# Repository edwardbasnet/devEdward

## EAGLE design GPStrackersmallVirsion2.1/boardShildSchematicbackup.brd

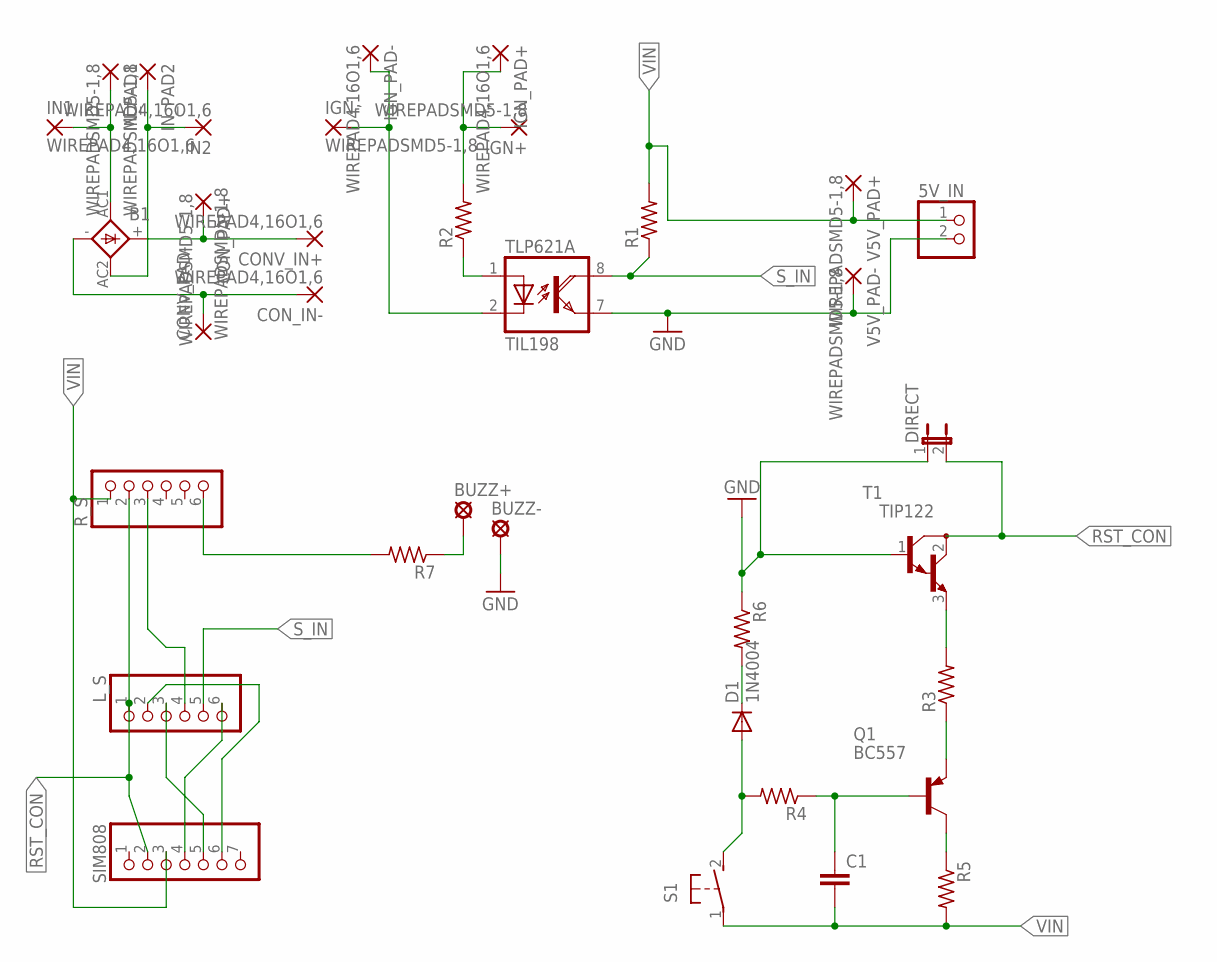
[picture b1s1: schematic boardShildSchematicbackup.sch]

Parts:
5V_IN: PINHD-1X2; 1X02
B1: FB15
BUZZ+: LSP10
BUZZ-: LSP10
C1: C2.5/5; C2.5-5
CONV_IN+: WIREPAD4,16O1,6; 4,16O1,6
CONV_PAD-: WIREPADSMD5-1,8; 5-1,8
CON_IN-: WIREPAD4,16O1,6; 4,16O1,6
CON_PAD+: WIREPADSMD5-1,8; 5-1,8
D1: 1N4004; DO41-10
DIRECT: JP1E; JP1
IGN+: WIREPADSMD5-1,8; 5-1,8
IGN-: WIREPADSMD5-1,8; 5-1,8
IGN_PAD+: WIREPAD4,16O1,6; 4,16O1,6
IGN_PAD-: WIREPAD4,16O1,6; 4,16O1,6
IN1, IN2: WIREPAD4,16O1,6; 4,16O1,6
IN_PAD1, IN_PAD2: WIREPADSMD5-1,8; 5-1,8
L_S: PINHD-1X6; 1X06
Q1: BC557; TO92
R1, R2, R3, R4, R5, R6, R7: R-US_0204/5; 0204/5
R_S: PINHD-1X6; 1X06
S1: 31-XX; B3F-31XX
SIM808: PINHD-1X7; 1X07
T1: TIP122; TO220
TLP621: TIL198; DIL08
V5V_PAD+, V5V_PAD-: WIREPADSMD5-1,8; 5-1,8

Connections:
GND: 5V_IN.2, BUZZ-.MP, DIRECT.1, R6.1, T1.1 (B), TLP621.7 (EMI), V5V_PAD-.1
unnamed: R2.1, TLP621.1 (A)
unnamed: B1.AC1, IN1.1, IN_PAD1.1
unnamed: IGN+.1, IGN_PAD+.1, R2.2
unnamed: L_S.4, R_S.3
unnamed: L_S.2, SIM808.6
unnamed: B1.-, CONV_PAD-.1, CON_IN-.1
unnamed: L_S.3, SIM808.5
unnamed: L_S.6, SIM808.4
unnamed: IGN-.1, IGN_PAD-.1, TLP621.2 (C)
unnamed: BUZZ+.MP, R7.1
unnamed: B1.AC2, IN2.1, IN_PAD2.1
unnamed: D1.A, R4.2, S1.2 (S)
unnamed: C1.1, Q1.2 (B), R4.1
unnamed: B1.+, CONV_IN+.1, CON_PAD+.1
unnamed: Q1.3 (C), R5.1
unnamed: Q1.1 (E), R3.1
unnamed: D1.C, R6.2
unnamed: R7.2, R_S.6
unnamed: R3.2, T1.3 (E)
RST_CON: DIRECT.2, L_S.1, R_S.2, SIM808.2, T1.2 (C)
S_IN: L_S.5, R1.1, TLP621.8 (COL)
VIN: 5V_IN.1, C1.2, R1.2, R5.2, R_S.1, S1.1, SIM808.3, V5V_PAD+.1

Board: 2 copper layers, 35 parts (0 on the bottom side), 23 nets, no tracks yet.

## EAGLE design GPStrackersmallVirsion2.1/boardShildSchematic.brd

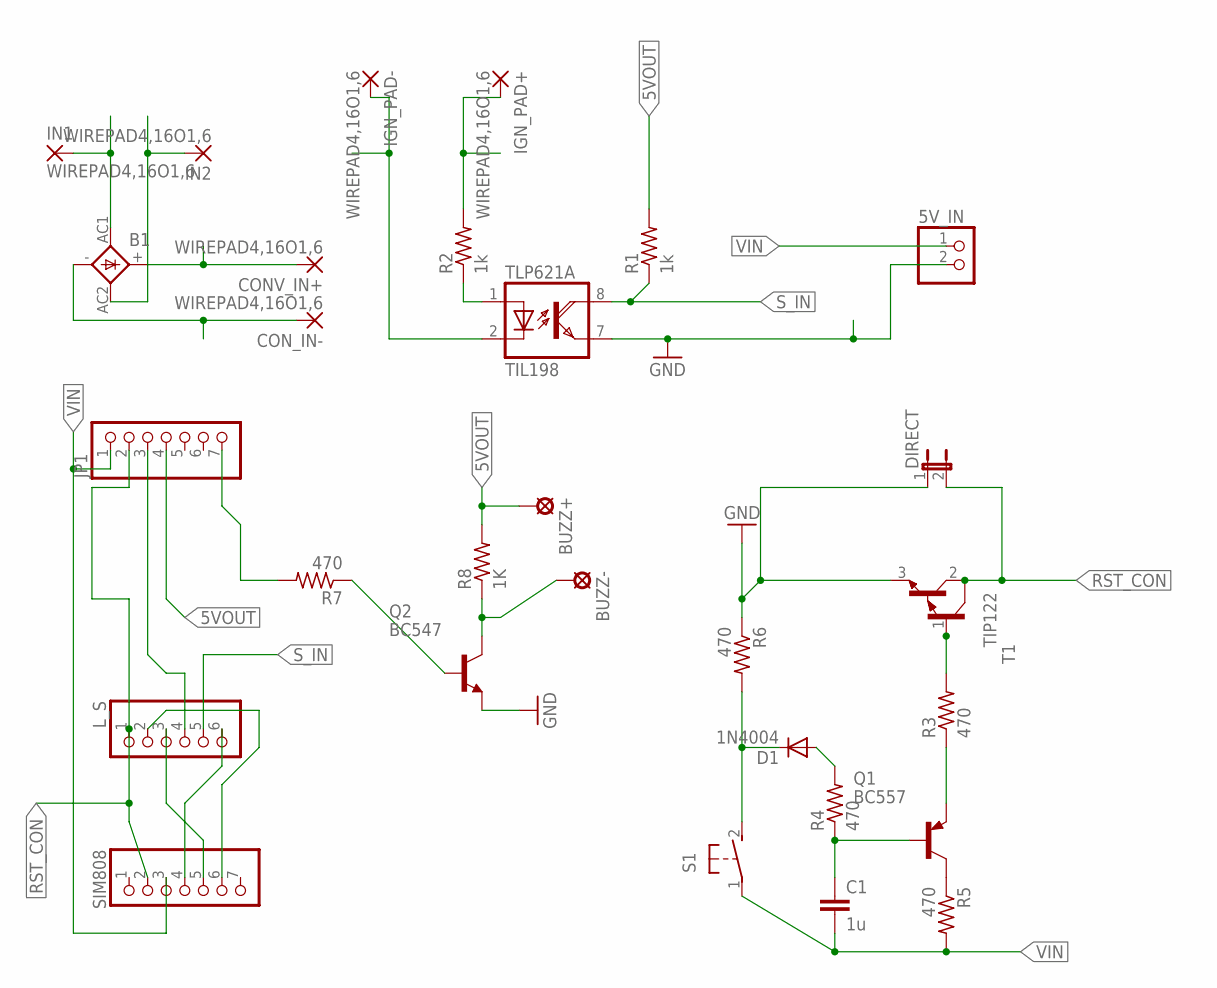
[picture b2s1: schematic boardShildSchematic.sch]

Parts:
5V_IN: PINHD-1X2; 1X02
B1: FB15
BUZZ+: LSP10
BUZZ-: LSP10
C1: 1u; C2.5-5
CONV_IN+: WIREPAD4,16O1,6; 4,16O1,6
CON_IN-: WIREPAD4,16O1,6; 4,16O1,6
D1: 1N4004; DO41-10
DIRECT: JP1E; JP1
IGN_PAD+: WIREPAD4,16O1,6; 4,16O1,6
IGN_PAD-: WIREPAD4,16O1,6; 4,16O1,6
IN1, IN2: WIREPAD4,16O1,6; 4,16O1,6
JP1: PINHD-1X7; 1X07
L_S: PINHD-1X6; 1X06
Q1: BC557; TO92
Q2: BC547; TO92
R1, R2: 1k; 0204/5
R3, R4, R5, R6, R7: 470; 0204/5
R8: 1K; 0204/5
S1: 31-XX; B3F-31XX
SIM808: PINHD-1X7; 1X07
T1: TIP122; TO220
TLP621: TIL198; DIL08

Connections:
5VOUT: BUZZ+.MP, JP1.4, R1.2, R8.2
GND: 5V_IN.2, DIRECT.1, Q2.1 (E), R6.1, T1.3 (E), TLP621.7 (EMI)
unnamed: R2.1, TLP621.1 (A)
unnamed: B1.AC1, IN1.1
unnamed: IGN_PAD+.1, R2.2
unnamed: JP1.3, L_S.4
unnamed: L_S.2, SIM808.6
unnamed: B1.-, CON_IN-.1
unnamed: L_S.3, SIM808.5
unnamed: L_S.6, SIM808.4
unnamed: IGN_PAD-.1, TLP621.2 (C)
unnamed: Q2.2 (B), R7.1
unnamed: B1.AC2, IN2.1
unnamed: D1.A, R4.2
unnamed: C1.1, Q1.2 (B), R4.1
unnamed: B1.+, CONV_IN+.1
unnamed: Q1.3 (C), R5.1
unnamed: Q1.1 (E), R3.1
unnamed: D1.C, R6.2, S1.2 (S)
unnamed: JP1.7, R7.2
unnamed: R3.2, T1.1 (B)
unnamed: BUZZ-.MP, Q2.3 (C), R8.1
RST_CON: DIRECT.2, JP1.2, L_S.1, SIM808.2, T1.2 (C)
S_IN: L_S.5, R1.1, TLP621.8 (COL)
VIN: 5V_IN.1, C1.2, JP1.1, R5.2, S1.1, SIM808.3

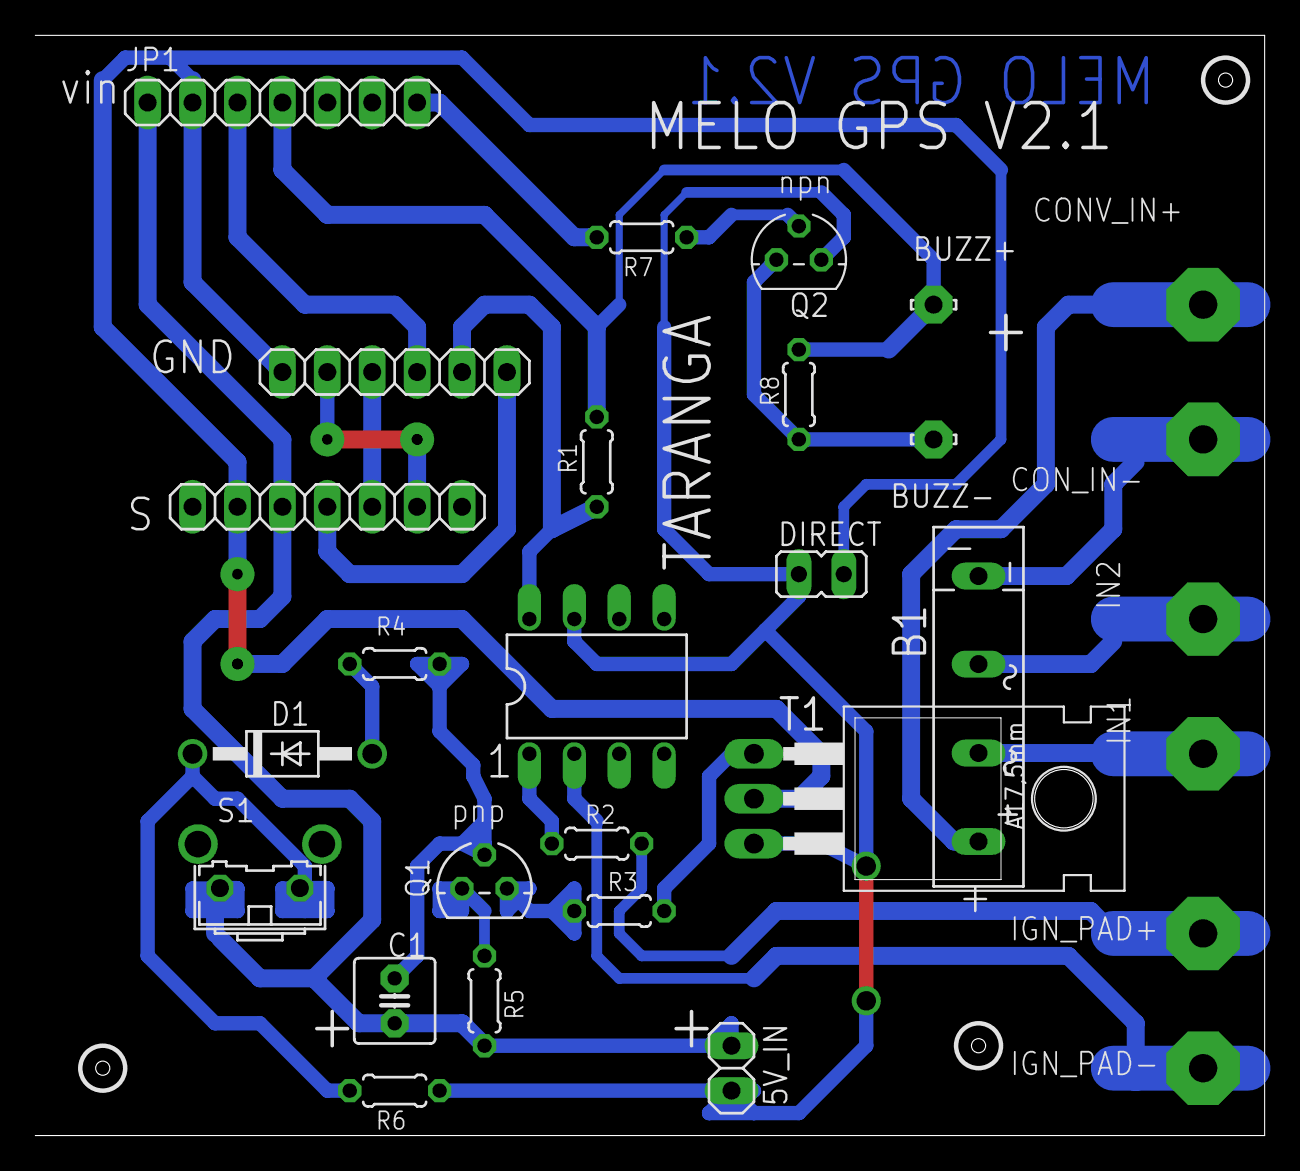
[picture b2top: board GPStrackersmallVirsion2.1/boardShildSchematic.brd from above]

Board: 2 copper layers, 69.5 x 62.2 mm, 29 parts (0 on the bottom side), 25 nets.

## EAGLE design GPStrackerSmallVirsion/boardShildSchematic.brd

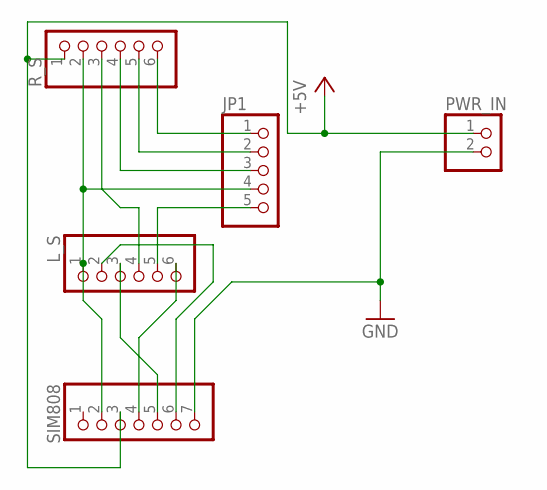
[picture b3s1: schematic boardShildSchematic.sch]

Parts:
JP1: PINHD-1X5; 1X05
L_S: PINHD-1X6; 1X06
PWR_IN: PINHD-1X2; 1X02
R_S: PINHD-1X6; 1X06
SIM808: PINHD-1X7; 1X07

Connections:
+5V: PWR_IN.1, R_S.1, SIM808.3
GND: PWR_IN.2, SIM808.7
unnamed: JP1.1, R_S.6
unnamed: JP1.2, R_S.5
unnamed: JP1.3, R_S.4
unnamed: L_S.4, R_S.3
unnamed: L_S.2, SIM808.6
unnamed: JP1.5, L_S.5
unnamed: JP1.4, L_S.1, R_S.2, SIM808.2
unnamed: L_S.3, SIM808.5
unnamed: L_S.6, SIM808.4

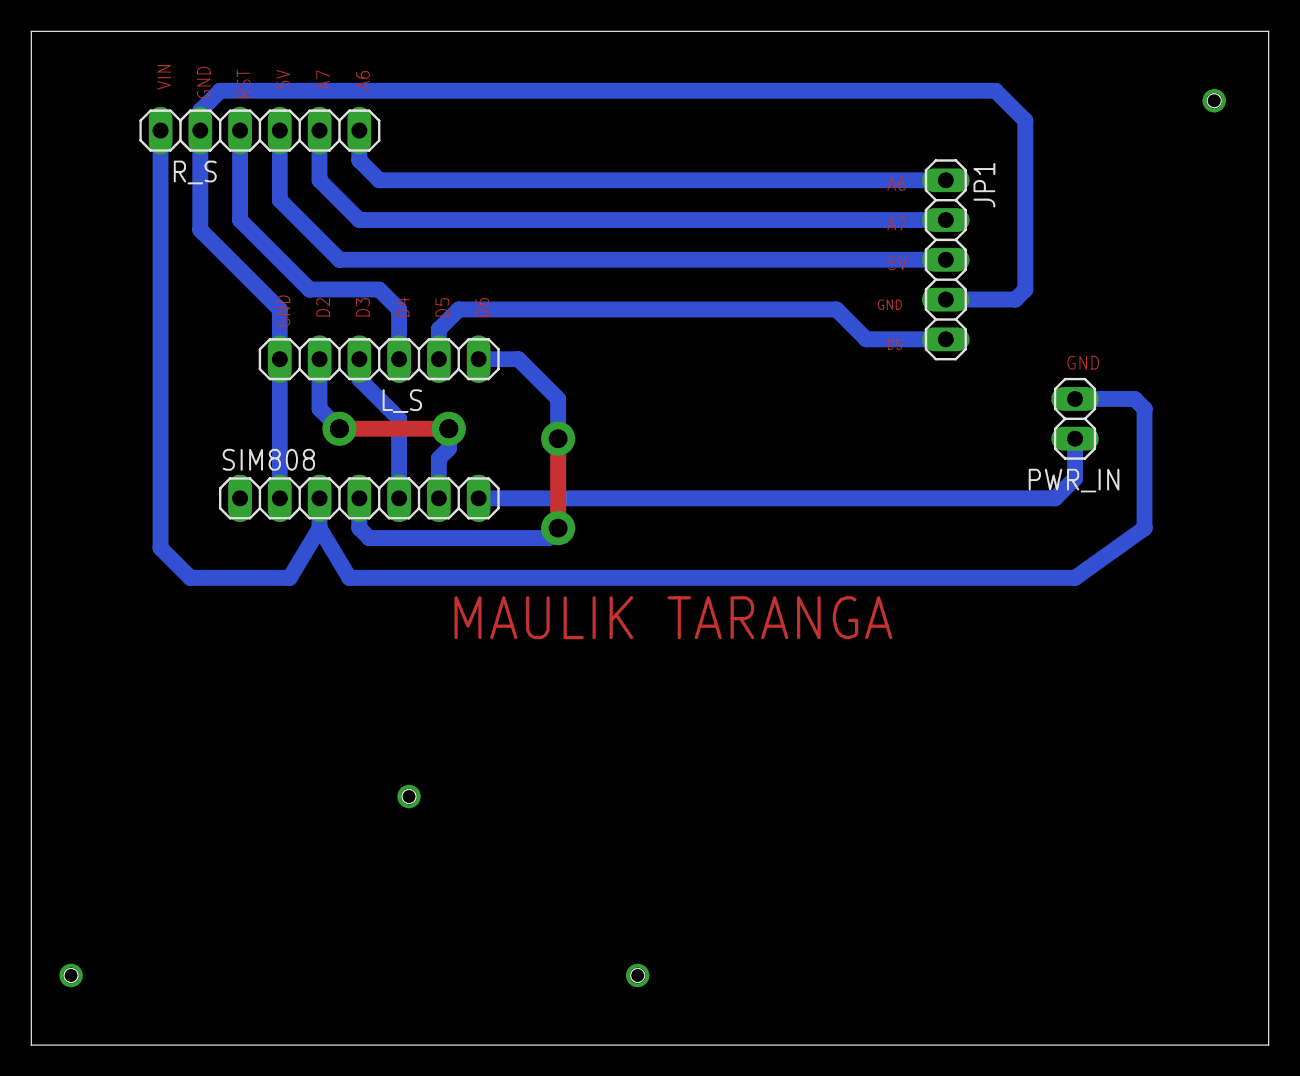
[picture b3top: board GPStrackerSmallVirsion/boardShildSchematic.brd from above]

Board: 2 copper layers, 79.0 x 64.8 mm, 5 parts (0 on the bottom side), 11 nets.

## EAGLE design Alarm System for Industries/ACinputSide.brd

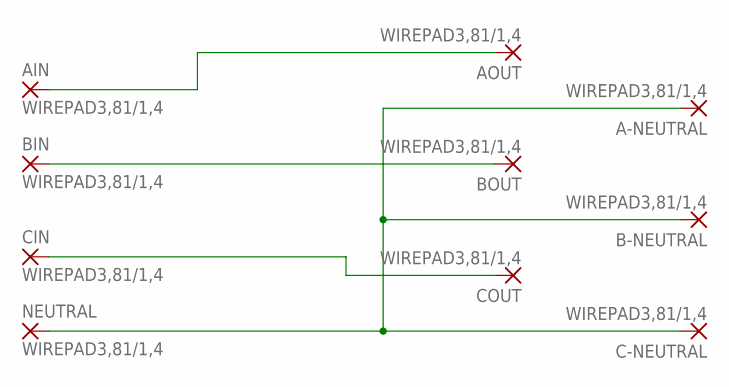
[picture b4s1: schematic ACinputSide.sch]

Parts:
A-NEUTRAL: WIREPAD3,81/1,4; 3,81/1,4
AIN: WIREPAD3,81/1,4; 3,81/1,4
AOUT: WIREPAD3,81/1,4; 3,81/1,4
B-NEUTRAL: WIREPAD3,81/1,4; 3,81/1,4
BIN: WIREPAD3,81/1,4; 3,81/1,4
BOUT: WIREPAD3,81/1,4; 3,81/1,4
C-NEUTRAL: WIREPAD3,81/1,4; 3,81/1,4
CIN: WIREPAD3,81/1,4; 3,81/1,4
COUT: WIREPAD3,81/1,4; 3,81/1,4
NEUTRAL: WIREPAD3,81/1,4; 3,81/1,4

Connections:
unnamed: A-NEUTRAL.1, B-NEUTRAL.1, C-NEUTRAL.1, NEUTRAL.1
unnamed: CIN.1, COUT.1
unnamed: BIN.1, BOUT.1
unnamed: AIN.1, AOUT.1

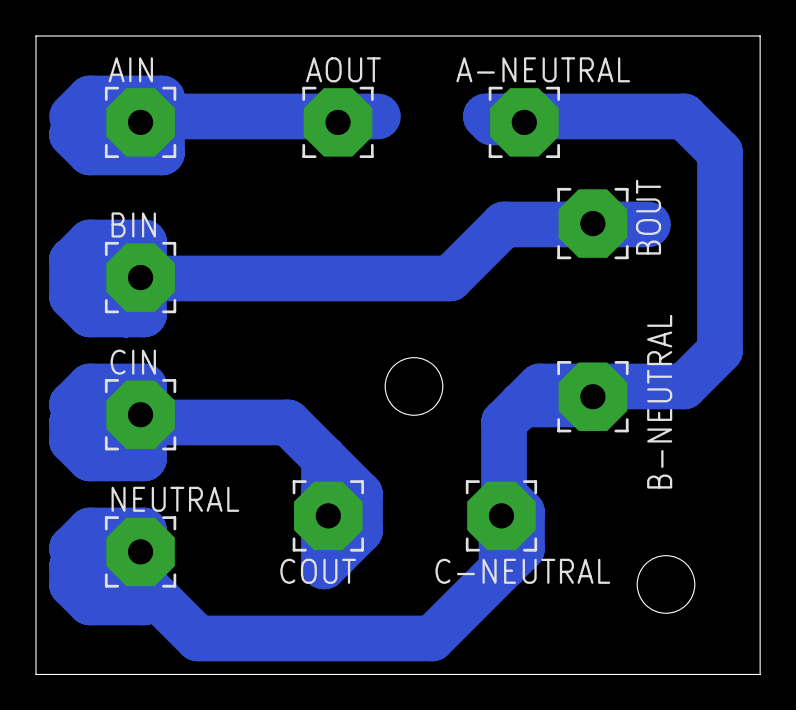
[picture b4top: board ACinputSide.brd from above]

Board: 2 copper layers, 40.2 x 35.5 mm, 10 parts (0 on the bottom side), 4 nets.

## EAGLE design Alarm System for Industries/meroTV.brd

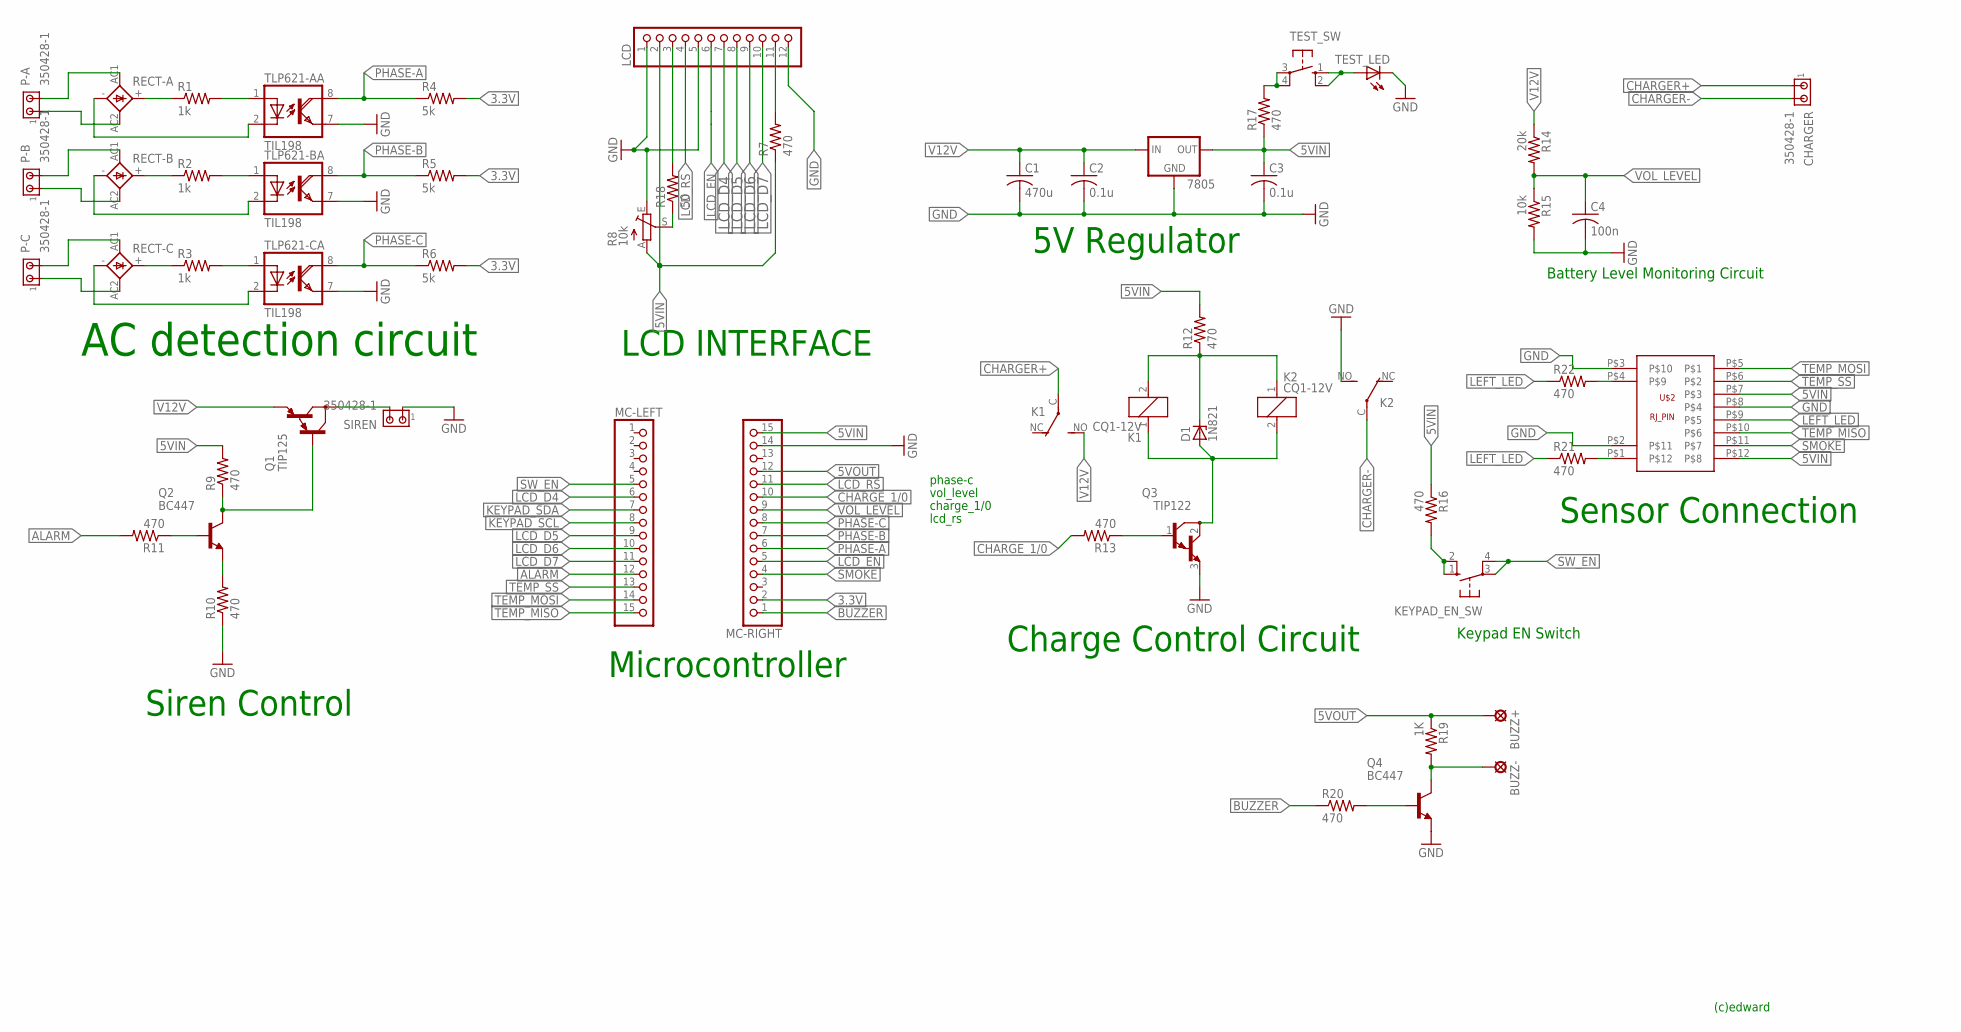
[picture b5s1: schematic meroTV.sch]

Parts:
7805: 78MXXL
BUZZ+: SE11
BUZZ-: SE11
C1: 470u; C025-040X050
C2, C3: 0.1u; C025-030X050
C4: 100n; C025-030X050
CHARGER: 350428-1
D1: 1N821; DO35Z10
K1, K2: CQ1-12V; CQ1
KEYPAD_EN_SW: 10-XX; B3F-10XX
LCD: PINHD-1X12; 1X12
MC-LEFT: PINHD-1X15; 1X15
MC-RIGHT: PINHD-1X15; 1X15
P-A: 350428-1
P-B: 350428-1
P-C: 350428-1
Q1: TIP125; TO220
Q2, Q4: BC447; TO92-EBC
Q3: TIP122; TO220
R1, R2, R3: 1k; 0204/5
R4, R5, R6: 5k; 0204/5
R7, R9, R10, R11, R12, R13, R16, R17, R20, R21, R22: 470; 0204/5
R8: 10k; B25V
R14: 20k; 0204/5
R15: 10k; 0204/5
R18: 50; 0204/5
R19: 1K; 0204/5
RECT-A: 2KBB-R
RECT-B: 2KBB-R
RECT-C: 2KBB-R
SIREN: 350428-1
TEST_LED: LED3MM
TEST_SW: 10-XX; B3F-10XX
TLP621-A, TLP621-B, TLP621-C: TIL198; DIL08
U$2: RJ45_EDWRJ45-DIL; RJ45-DIL

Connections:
3.3V: MC-RIGHT.2, R4.2, R5.2, R6.2
5VIN: 7805.OUT, C3.1, LCD.2, MC-RIGHT.15, R7.1, R8.A, R9.2, R12.2, R16.1, R17.1, U$2.P$7, U$2.P$12
5VOUT: BUZZ+.MP, MC-RIGHT.12, R19.1
ALARM: MC-LEFT.12, R11.2
BUZZER: MC-RIGHT.1, R20.1
CHARGER+: CHARGER.1, K1.C
CHARGER-: CHARGER.2, K2.C
CHARGE_1/0: MC-RIGHT.10, R13.2
GND: 7805.GND, C1.2, C2.2, C3.2, C4.2, K2.NO (S), LCD.1, LCD.5, LCD.12, MC-RIGHT.14, Q3.3 (E), Q4.E, R8.E, R10.1, R15.2, SIREN.1, TEST_LED.K (C), TLP621-A.7 (EMI), TLP621-B.7 (EMI), TLP621-C.7 (EMI), U$2.P$2, U$2.P$3, U$2.P$8
KEYPAD_SCL: MC-LEFT.8
KEYPAD_SDA: MC-LEFT.7
LCD_D4: LCD.7, MC-LEFT.6
LCD_D5: LCD.8, MC-LEFT.9
LCD_D6: LCD.9, MC-LEFT.10
LCD_D7: LCD.10, MC-LEFT.11
LCD_EN: LCD.6, MC-RIGHT.5
LCD_RS: LCD.4, MC-RIGHT.11
LEFT_LED: R21.1, R22.1, U$2.P$9
unnamed: Q1.2 (C), SIREN.2
unnamed: P-A.1, RECT-A.AC2
unnamed: P-B.2, RECT-B.AC1
unnamed: P-B.1, RECT-B.AC2
unnamed: P-C.2, RECT-C.AC1
unnamed: P-C.1, RECT-C.AC2
unnamed: R1.1, RECT-A.+
unnamed: R2.1, RECT-B.+
unnamed: R1.2, TLP621-A.1 (A)
unnamed: R2.2, TLP621-B.1 (A)
unnamed: R3.2, TLP621-C.1 (A)
unnamed: R3.1, RECT-C.+
unnamed: RECT-A.-, TLP621-A.2 (C)
unnamed: RECT-B.-, TLP621-B.2 (C)
unnamed: RECT-C.-, TLP621-C.2 (C)
unnamed: D1.C, K1.2, K2.1, R12.1
unnamed: KEYPAD_EN_SW.1 (S), KEYPAD_EN_SW.2 (S1), R16.2
unnamed: D1.A, K1.1, K2.2, Q3.2 (C)
unnamed: Q1.1 (B), Q2.C, R9.1
unnamed: Q2.E, R10.2
unnamed: Q2.B, R11.1
unnamed: Q3.1 (B), R13.1
unnamed: R17.2, TEST_SW.3, TEST_SW.4 (P1)
unnamed: TEST_LED.A, TEST_SW.1 (S), TEST_SW.2 (S1)
unnamed: LCD.11, R7.2
unnamed: R8.S, R18.1
unnamed: LCD.3, R18.2
unnamed: BUZZ-.MP, Q4.C, R19.2
unnamed: R22.2, U$2.P$4
unnamed: R21.2, U$2.P$1
unnamed: Q4.B, R20.2
P-A: P-A.2, RECT-A.AC1
PHASE-A: MC-RIGHT.6, R4.1, TLP621-A.8 (COL)
PHASE-B: MC-RIGHT.7, R5.1, TLP621-B.8 (COL)
PHASE-C: MC-RIGHT.8, R6.1, TLP621-C.8 (COL)
SMOKE: MC-RIGHT.4, U$2.P$11
SW_EN: KEYPAD_EN_SW.3, KEYPAD_EN_SW.4 (P1), MC-LEFT.5
TEMP_MISO: MC-LEFT.15, U$2.P$10
TEMP_MOSI: MC-LEFT.14, U$2.P$5
TEMP_SS: MC-LEFT.13, U$2.P$6
V12V: 7805.IN, C1.1, C2.1, K1.NO (S), Q1.3 (E), R14.1
VOL_LEVEL: C4.1, MC-RIGHT.9, R14.2, R15.1

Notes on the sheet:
AC detection circuit
LCD INTERFACE
5V Regulator
Microcontroller
Siren Control
Charge Control Circuit
Sensor Connection
Battery Level Monitoring Circuit
Keypad EN Switch
(c)edward
phase-c
vol_level
charge_1/0
lcd_rs

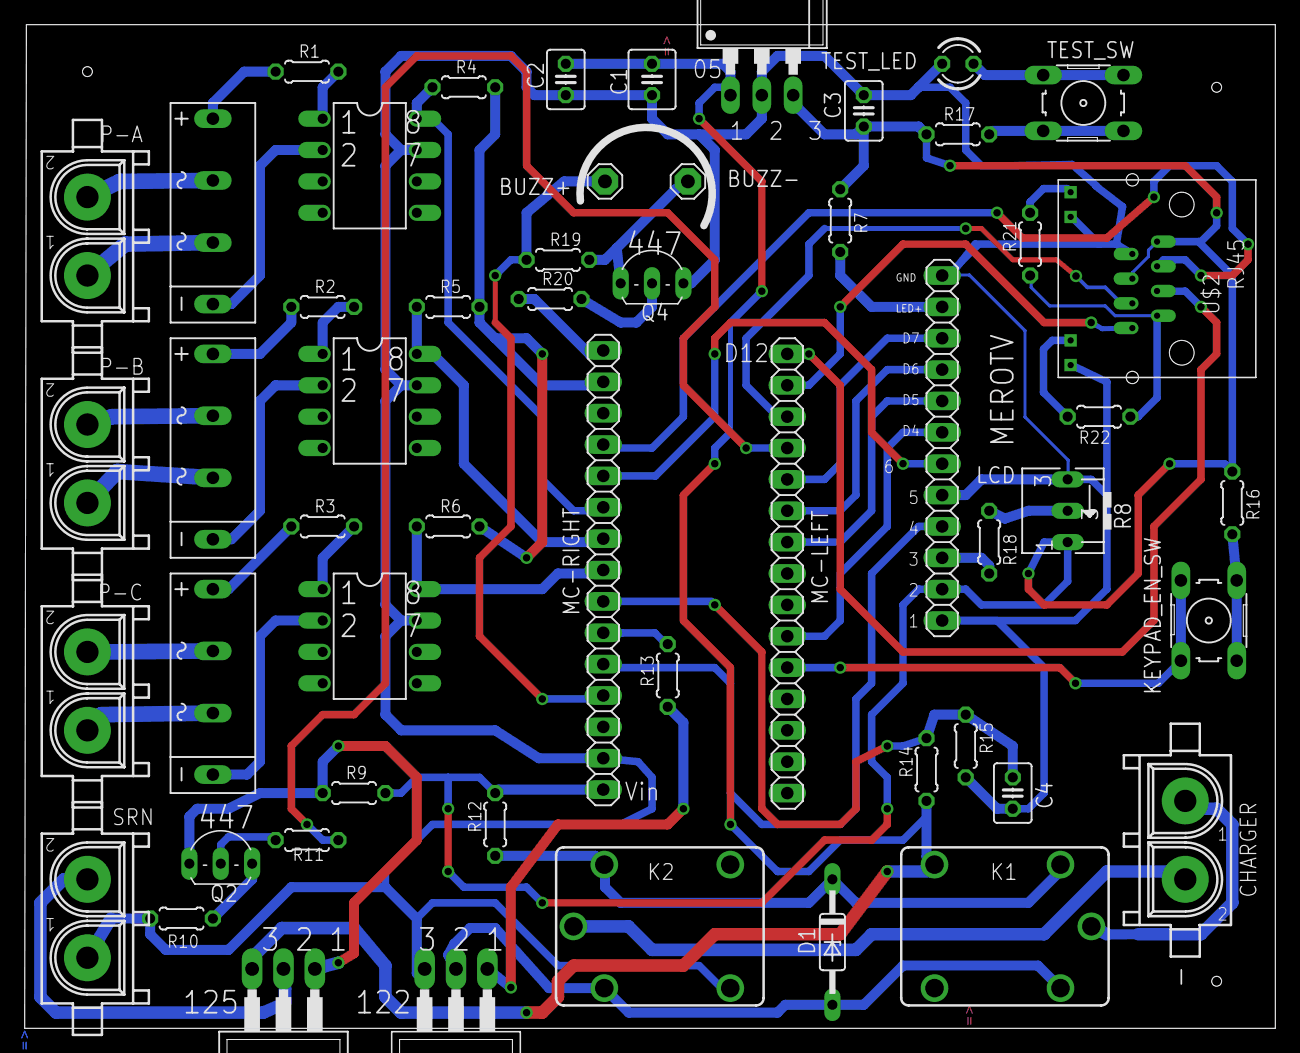
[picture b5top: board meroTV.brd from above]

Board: 2 copper layers, 101.3 x 81.3 mm, 54 parts (0 on the bottom side), 58 nets.

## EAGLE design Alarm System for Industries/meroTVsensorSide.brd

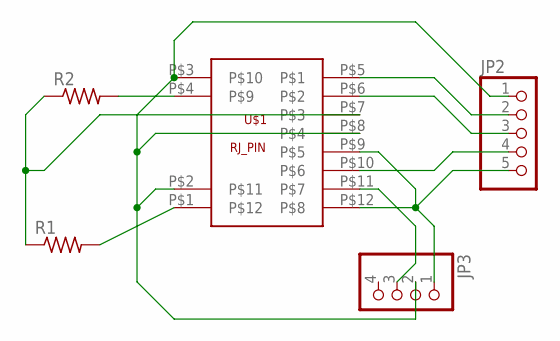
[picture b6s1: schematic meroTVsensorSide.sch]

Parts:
JP2: PINHD-1X5; 1X05
JP3: PINHD-1X4; 1X04
R1, R2: R-US_0204/7; 0204/7
U$1: RJ45_EDWRJ45-DIL; RJ45-DIL

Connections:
unnamed: JP2.5, JP3.1, U$1.P$9, U$1.P$12
unnamed: JP2.1, JP3.2, U$1.P$2, U$1.P$3, U$1.P$8
unnamed: JP3.3, U$1.P$11
unnamed: R1.2, U$1.P$1
unnamed: R2.2, U$1.P$4
unnamed: R1.1, R2.1, U$1.P$7
unnamed: JP2.2, U$1.P$5
unnamed: JP2.3, U$1.P$6
unnamed: JP2.4, U$1.P$10

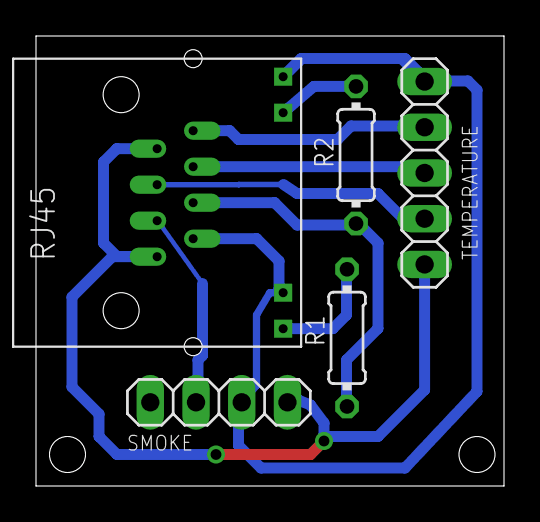
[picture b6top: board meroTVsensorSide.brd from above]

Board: 2 copper layers, 26.0 x 25.0 mm, 5 parts (0 on the bottom side), 9 nets.

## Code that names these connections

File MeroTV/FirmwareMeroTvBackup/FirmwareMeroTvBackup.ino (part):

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 * wiper to LCD VO pin (pin 3) 
*/

#define LCD_RS 18
#define LCD_EN 15
#define LCD_D4 3
#define LCD_D5 6
#define LCD_D6 7
#define LCD_D7 8

#include <LiquidCrystal.h>

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/************************************************************************************/

//  Voltage level
#define VOL_LEVEL A6
float initVol, finalVol;
//  Charge Activation
#define CHARGE 19
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//Detect interrupt; if happen then activate touchpad and store the inputted value as Threshold

/*********** Smoke **********/
#define SMOKE A0
/****************************/

//  THRESHOLD voltage value for activate/deactivate the alerting mechanism
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  lcd.begin(20,4);
    
// Battery Voltage and activate/deactivate charging mechanism
  pinMode(VOL_LEVEL, INPUT);
  pinMode(CHARGE, OUTPUT);
  initVol = readVoltage();
  
//Initialize Smoke Sensor
  pinMode(SMOKE, INPUT);


//Initialize Temperature Sensor and Callibrate
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  float vout = 0.0, vin = 0.0, R1 = 22000.0, R2 = 10000.0; 
  int sensorValue = 0;
  //for(int k = 1; k<=20; k++){
  sensorValue = analogRead(VOL_LEVEL); //read the A0 pin value
  //Serial.println(sensorValue);
  //delay(20);
  //}
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
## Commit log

2026-01-04 file added
